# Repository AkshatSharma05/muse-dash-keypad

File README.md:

# muse-dash-keypad
A 4-key keypad designed specifically to play Muse Dash using the ATmega32U4 MCU

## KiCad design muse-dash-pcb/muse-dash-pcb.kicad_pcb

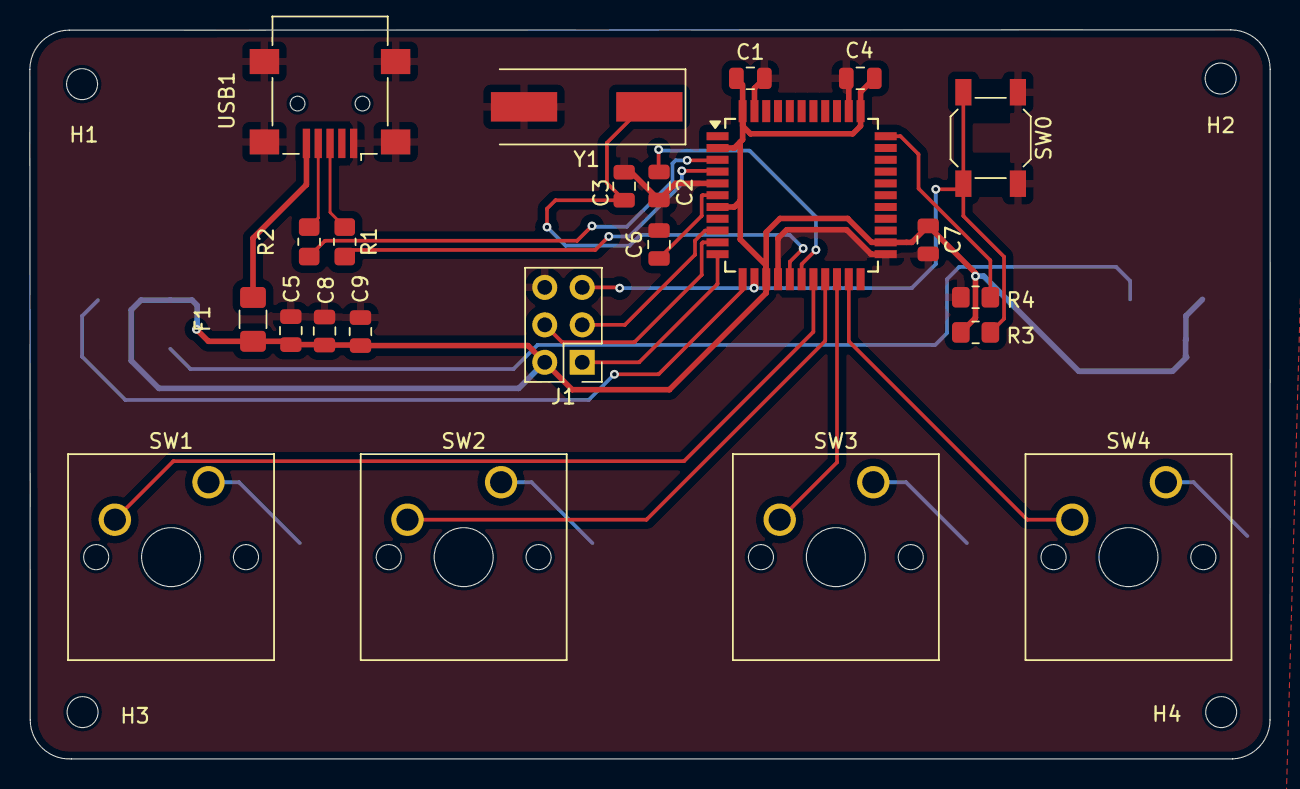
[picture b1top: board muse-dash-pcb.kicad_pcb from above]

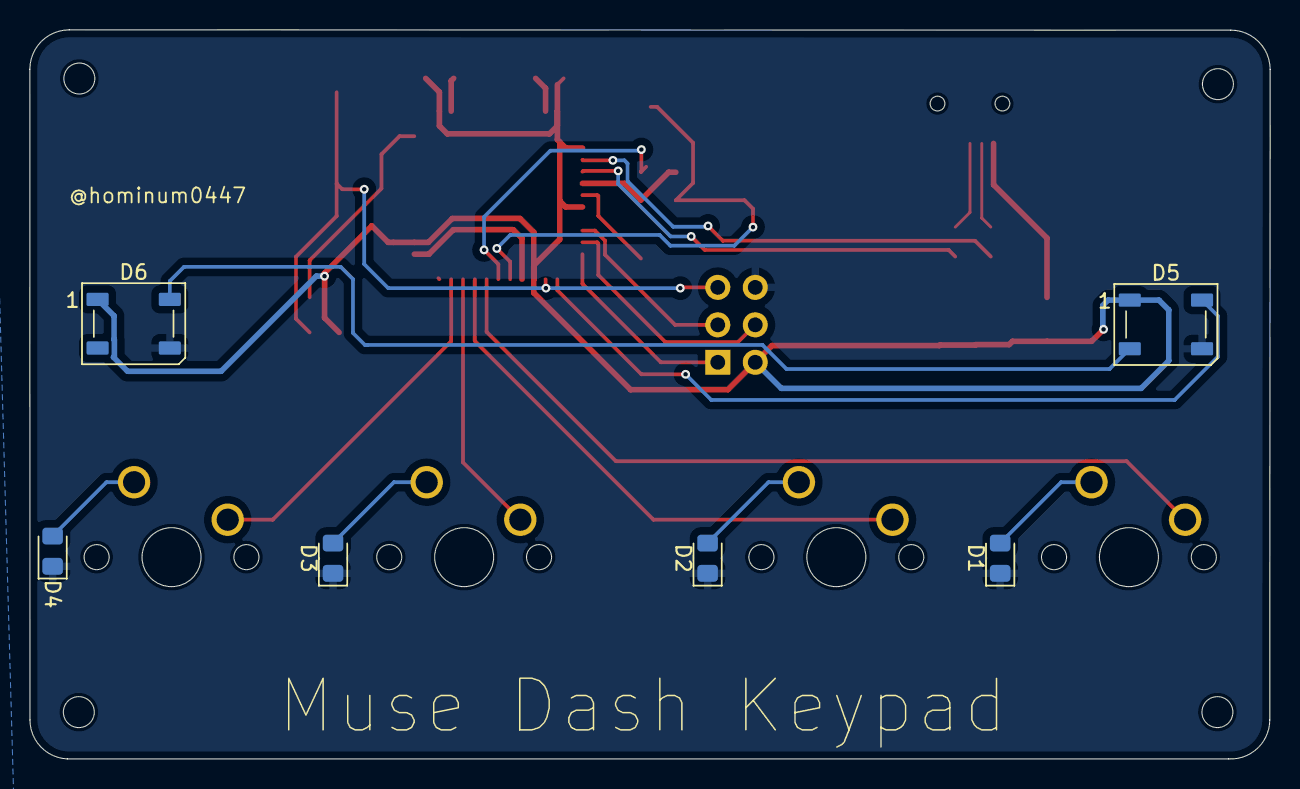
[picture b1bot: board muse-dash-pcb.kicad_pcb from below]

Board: 2 copper layers, 84.1 x 49.4 mm, 33 parts (6 on the bottom side), 25 nets.

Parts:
C1, C4, C5, C8, C9: 0.1uF; C_0805_2012Metric
C2, C3: 22uF; C_0805_2012Metric
C6: 1uF; C_0805_2012Metric
C7: 10uF; C_0805_2012Metric
D1, D2, D3, D4: D; D_0805_2012Metric_Pad1.15x1.40mm_HandSolder
D5, D6: WS2812B; LED_WS2812B_PLCC4_5.0x5.0mm_P3.2mm
F1: 500mA; Fuse_1206_3216Metric_Pad1.42x1.75mm_HandSolder
H1, H2, H3, H4: MountingHole; MountingHole_2.1mm
J1: AVR-ISP-6; PinHeader_2x03_P2.54mm_Vertical
R1, R2: 22; R_0805_2012Metric_Pad1.20x1.40mm_HandSolder
R3: 10K; R_0805_2012Metric_Pad1.20x1.40mm_HandSolder
R4: 10k; R_0805_2012Metric_Pad1.20x1.40mm_HandSolder
SW0: SW_Push; SW_SPST_SKQG_WithStem
SW1, SW2, SW3, SW4: CherryMX; SW_Cherry_MX_1.00u_PCB
U1: ATmega32U4-A; TQFP-44_10x10mm_P0.8mm
USB1: Molex-0548190589; USB_Mini-B_Lumberg_2486_01_Horizontal
Y1: Crystal_GND24; Crystal_SMD_HC49-SD

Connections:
+5V: C1.1, C4.1, C5.1, C7.1, C8.2, C9.1, D5.1 (VDD), D6.1 (VDD), F1.2, J1.2 (VCC), R3.1, U1.2 (UVCC), U1.7 (VBUS), U1.14 (VCC), U1.24 (AVCC), U1.34 (VCC), U1.44 (AVCC)
D+: R1.1, USB1.3 (D+)
D-: R2.1, USB1.4 (D-)
GND: C1.2, C2.1, C3.1, C4.2, C5.2, C6.2, C7.2, C8.1, C9.2, D1.1 (K), D2.1 (K), D3.1 (K), D4.1 (K), D5.3 (VSS), D6.3 (VSS), J1.6 (GND), R4.2, SW0.1, U1.5 (UGND), U1.15 (GND), U1.23 (GND), U1.35 (GND), U1.43 (GND), USB1.1 (GND), USB1.6 (SHIELD), Y1.2
MISO: J1.1 (MISO), U1.11 (PB3)
MOSI: J1.4 (MOSI), U1.10 (PB2)
unnamed: D1.2 (A), SW1.1
unnamed: D2.2 (A), SW2.1
unnamed: D3.2 (A), SW3.1
unnamed: D4.2 (A), SW4.1
unnamed: D5.2 (DOUT), D6.4 (DIN)
unnamed: R1.2, U1.4 (D+)
unnamed: R2.2, U1.3 (D-)
unnamed: C6.1, U1.6 (UCAP)
unnamed: C2.2, U1.17 (XTAL1)
unnamed: C3.2, U1.16 (XTAL2), Y1.1
unnamed: R4.1, U1.33 (~HWB/PE2)
RESET: J1.5 (~RST), R3.2, SW0.2, U1.13 (~RESET)
SCK: J1.3 (SCK), U1.9 (PB1)
SW1: SW1.2, U1.18 (PD0)
SW2: SW2.2, U1.19 (PD1)
SW3: SW3.2, U1.20 (PD2)
SW4: SW4.2, U1.21 (PD3)
UNDERGLOW: D5.4 (DIN), U1.12 (PB7)
VCC: F1.1, USB1.5 (VBUS)

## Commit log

2024-12-20 initialized project
2024-12-20 added submodules
2024-12-20 added symbols and footprints
2024-12-20 added mcu and switches nw
2024-12-25 added footprints
2024-12-28 completed pcb design
2024-12-29 general fixes
2024-12-29 added 3d models for switches
2024-12-29 fixed routes and added mounting holes
2024-12-31 added ISP Interface
2024-12-31 added underglow leds
2025-01-01 added ground fills
2025-01-04 cleaned up routing
2025-01-04 added missing resistor value
2025-01-05 changed ISP header footprint, fixed Ground plane and improved routing
2025-01-30 fixed back layer routing
2025-01-30 changed oscillator footprint
2025-02-12 silkscreen text added
2025-02-27 inverted text color
